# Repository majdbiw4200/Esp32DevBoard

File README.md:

# Esp32DevBoard
ESP32-WROOM-32 microcontroller development board

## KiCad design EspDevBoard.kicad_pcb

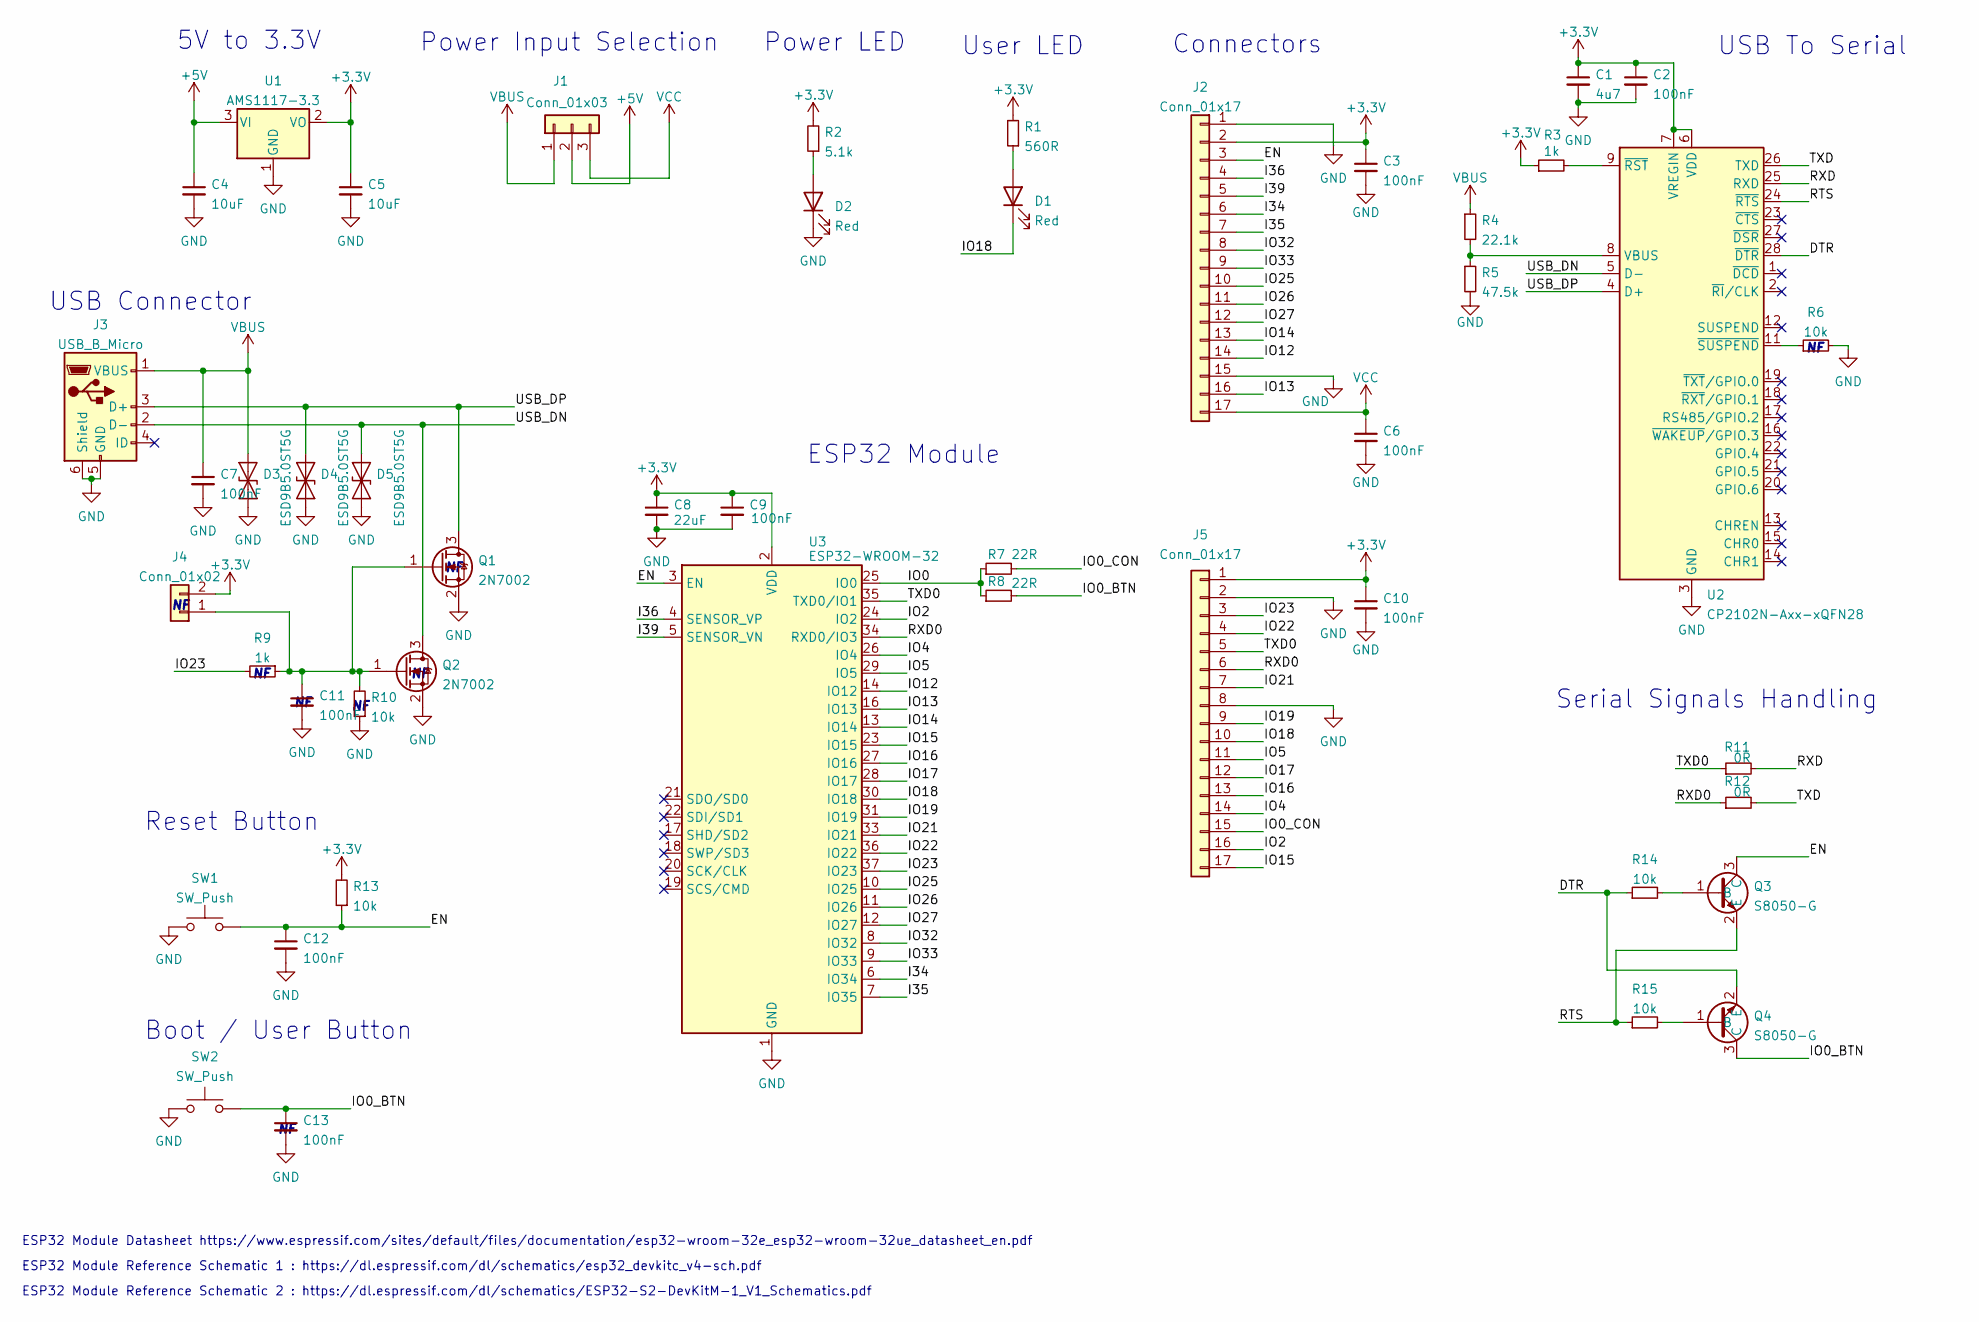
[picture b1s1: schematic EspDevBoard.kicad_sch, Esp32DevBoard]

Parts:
C1: 4u7; C_0402_1005Metric; LCSC Part # C368809
C2, C3, C6, C7, C9, C10, C11, C12, C13: 100nF; C_0402_1005Metric; LCSC Part # C1525
C4, C5: 10uF; C_0402_1005Metric; LCSC Part # C315248
C8: 22uF; C_0805_2012Metric; LCSC Part # C45783
D1, D2: Red; LED_0805_2012Metric; LCSC Part # C113551
D3, D4, D5: ESD9B5.0ST5G; D_SOD-923; LCSC Part # C383211
J1: Conn_01x03; Molex_PicoBlade_53048-0310_1x03_P1.25mm_Horizontal; LCSC Part # C505275
J2, J5: Conn_01x17; Molex_SL_171971-0017_1x17_P2.54mm_Vertical
J3: USB_B_Micro; USB_Micro-B_Molex_47346-0001; LCSC Part # C132560
J4: Conn_01x02; Molex_PicoBlade_53048-0210_1x02_P1.25mm_Horizontal; LCSC Part # C505099
Q1, Q2: 2N7002; SOT-23; LCSC Part # C8545
Q3, Q4: S8050-G; SOT-23; LCSC Part # C164885
R1: 560R; R_0402_1005Metric; LCSC Part # C25126
R2: 5.1k; R_0402_1005Metric; LCSC Part # C25905
R3, R9: 1k; R_0402_1005Metric; LCSC Part # C11702
R4: 22.1k; R_0402_1005Metric; LCSC Part # C43473
R5: 47.5k; R_0402_1005Metric; LCSC Part # C25896
R6, R10, R13, R14, R15: 10k; R_0402_1005Metric; LCSC Part # C25804
R7, R8: 22R; R_0402_1005Metric; LCSC Part # C25804
R11, R12: 0R; R_0402_1005Metric; LCSC Part # C17168
SW1, SW2: SW_Push; SW_Push_1P1T_NO_6x6mm_H9.5mm; LCSC Part # C255812
U1: AMS1117-3.3; SOT-223-3_TabPin2; LCSC Part # C347222
U2: CP2102N-Axx-xQFN28; QFN-28-1EP_5x5mm_P0.5mm_EP3.35x3.35mm; LCSC Part # C964632
U3: ESP32-WROOM-32; LCSC Part # C701342

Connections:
+3V3: C1.1, C2.1, C3.1, C5.1, C8.1, C9.1, C10.1, J2.2, J4.2, J5.1, R1.2, R2.2, R3.1, R13.2, U1.2 (VO), U2.6 (VDD), U2.7 (VREGIN), U3.2 (VDD)
+5V: C4.1, J1.2, U1.3 (VI)
/DTR: Q4.2 (E), R14.1, U2.28 (~DTR)
/EN: C12.1, J2.3, Q3.3 (C), R13.1, SW1.2, U3.3 (EN)
/I34: J2.6, U3.6 (IO34)
/I35: J2.7, U3.7 (IO35)
/I36: J2.4, U3.4 (SENSOR_VP)
/I39: J2.5, U3.5 (SENSOR_VN)
/IO0: R7.1, R8.1, U3.25 (IO0)
/IO0_BTN: C13.1, Q4.3 (C), R8.2, SW2.2
/IO0_CON: J5.15, R7.2
/IO2: J5.16, U3.24 (IO2)
/IO4: J5.14, U3.26 (IO4)
/IO5: J5.11, U3.29 (IO5)
/IO12: J2.14, U3.14 (IO12)
/IO13: J2.16, U3.16 (IO13)
/IO14: J2.13, U3.13 (IO14)
/IO15: J5.17, U3.23 (IO15)
/IO16: J5.13, U3.27 (IO16)
/IO17: J5.12, U3.28 (IO17)
/IO18: D1.1 (K), J5.10, U3.30 (IO18)
/IO19: J5.9, U3.31 (IO19)
/IO21: J5.7, U3.33 (IO21)
/IO22: J5.4, U3.36 (IO22)
/IO23: J5.3, R9.2, U3.37 (IO23)
/IO25: J2.10, U3.10 (IO25)
/IO26: J2.11, U3.11 (IO26)
/IO27: J2.12, U3.12 (IO27)
/IO32: J2.8, U3.8 (IO32)
/IO33: J2.9, U3.9 (IO33)
/RTS: Q3.2 (E), R15.1, U2.24 (~RTS)
/RXD: R11.2, U2.25 (RXD)
/RXD0: J5.6, R12.1, U3.34 (RXD0/IO3)
/TXD: R12.2, U2.26 (TXD)
/TXD0: J5.5, R11.1, U3.35 (TXD0/IO1)
/USB_DN: D5.2 (A2), J3.2 (D-), Q2.3 (D), U2.5 (D-)
/USB_DP: D4.2 (A2), J3.3 (D+), Q1.3 (D), U2.4 (D+)
GND: C1.2, C2.2, C3.2, C4.2, C5.2, C6.2, C7.2, C8.2, C9.2, C10.2, C11.2, C12.2, C13.2, D2.1 (K), D3.1 (A1), D4.1 (A1), D5.1 (A1), J2.1, J2.15, J3.5 (GND), J3.6 (Shield), J5.2, J5.8, Q1.2 (S), Q2.2 (S), R5.2, R6.2, R10.1, SW1.1, SW2.1, U1.1 (GND), U2.3 (GND), U2.29 (GND), U3.1 (GND), U3.15 (GND), U3.38 (GND), U3.39 (GND)
unnamed: C11.1, J4.1, Q1.1 (G), Q2.1 (G), R9.1, R10.2
unnamed: D1.2 (A), R1.1
unnamed: D2.2 (A), R2.1
unnamed: Q3.1 (B), R14.2
unnamed: Q4.1 (B), R15.2
unnamed: R3.2, U2.9 (~RST)
unnamed: R4.2, R5.1, U2.8 (VBUS)
unnamed: R6.1, U2.11 (~SUSPEND)
VBUS: C7.1, D3.2 (A2), J1.1, J3.1 (VBUS), R4.1
VCC: C6.1, J1.3, J2.17

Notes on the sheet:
Power LED
Reset Button
User LED
ESP32 Module Datasheet https://www.espressif.com/sites/default/files/documentation/esp32-wroom-32e_esp32-wroom-32ue_datasheet_en.pdf
Connectors
USB To Serial
USB Connector
ESP32 Module
Serial Signals Handling
ESP32 Module Reference Schematic 2 : https://dl.espressif.com/dl/schematics/ESP32-S2-DevKitM-1_V1_Schematics.pdf
ESP32 Module Reference Schematic 1 : https://dl.espressif.com/dl/schematics/esp32_devkitc_v4-sch.pdf
Boot / User Button
Power Input Selection
5V to 3.3V

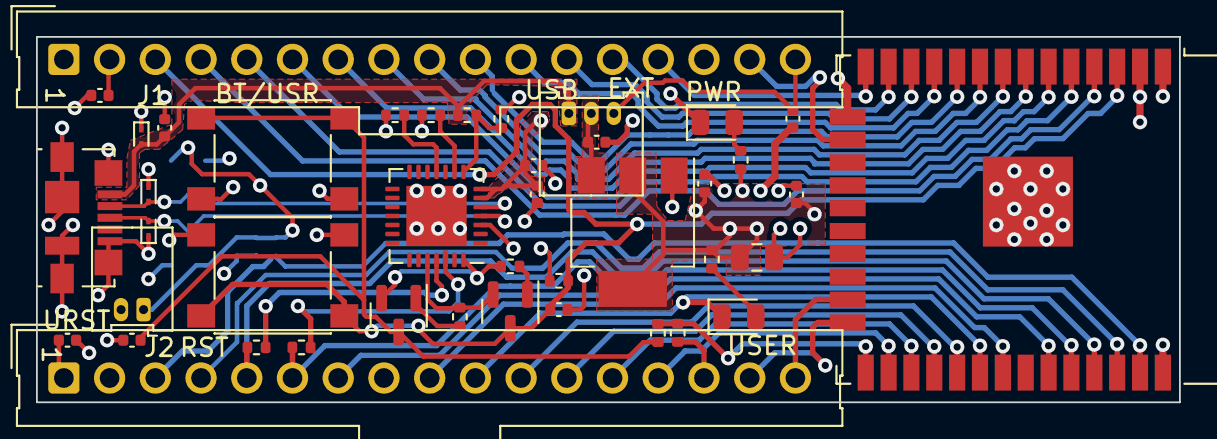
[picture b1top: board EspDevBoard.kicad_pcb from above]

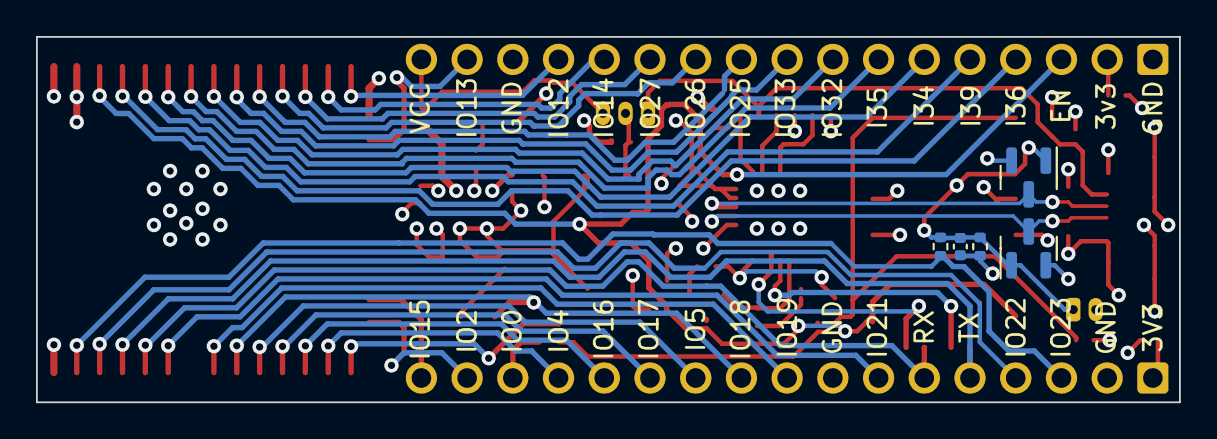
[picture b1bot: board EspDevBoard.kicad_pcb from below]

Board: 4 copper layers, 63.5 x 20.3 mm, 47 parts (5 on the bottom side), 48 nets.

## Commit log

2023-01-04 Add project 3rd view picture
